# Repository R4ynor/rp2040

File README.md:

# rp2040
 rp2040 poor man's edition

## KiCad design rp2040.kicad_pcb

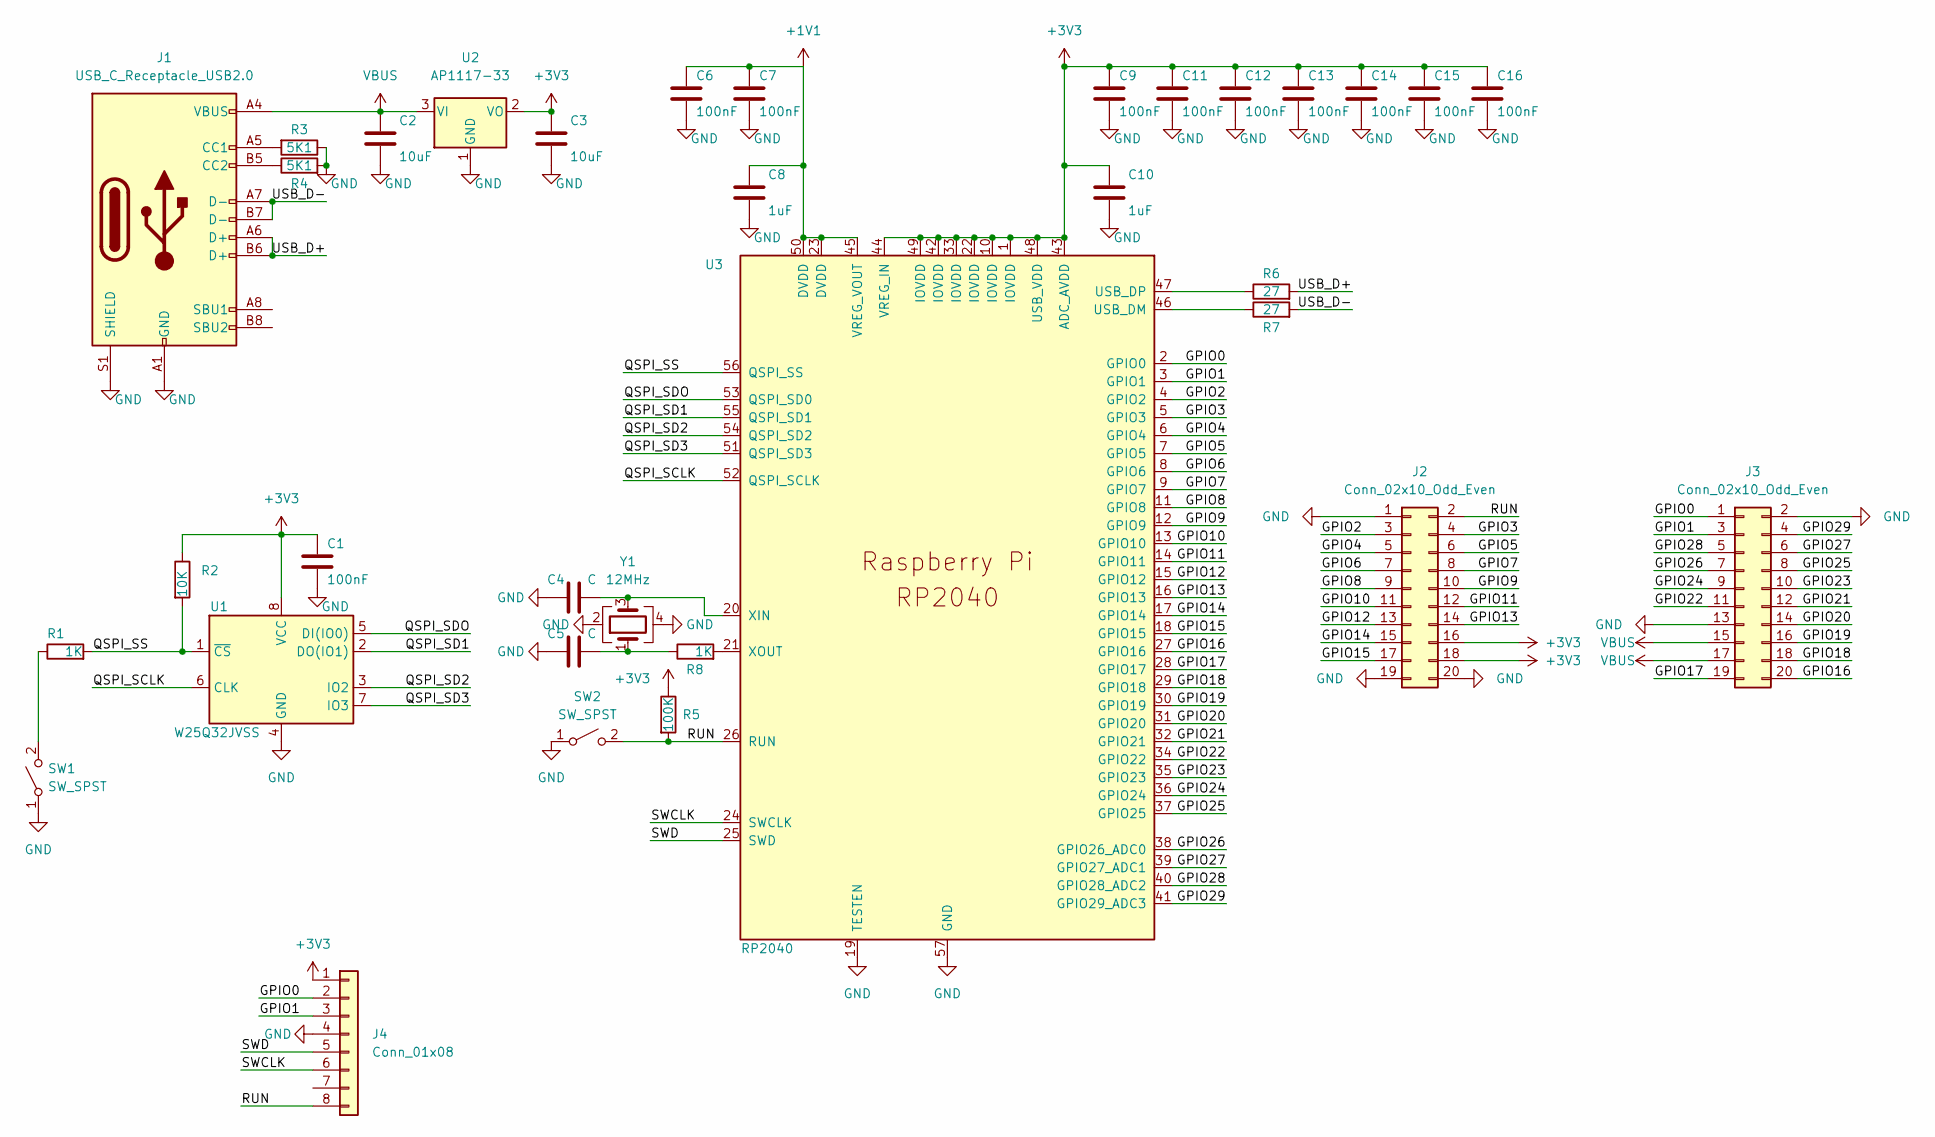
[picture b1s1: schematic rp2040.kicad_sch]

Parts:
C1, C6, C7, C9, C11, C12, C13, C14, C15, C16: 100nF; C_0402_1005Metric_Pad0.74x0.62mm_HandSolder
C2, C3: 10uF; C_0603_1608Metric_Pad1.08x0.95mm_HandSolder
C4, C5: C; C_0402_1005Metric_Pad0.74x0.62mm_HandSolder
C8, C10: 1uF; C_0402_1005Metric_Pad0.74x0.62mm_HandSolder
J1: USB_C_Receptacle_USB2.0; USB_C_Receptacle_XKB_U262-16XN-4BVC11
J2, J3: Conn_02x10_Odd_Even; PinHeader_2x10_P2.54mm_Vertical
J4: Conn_01x08; SOIC_clipProgSmall
R1, R8: 1K; R_0402_1005Metric_Pad0.72x0.64mm_HandSolder
R2: 10K; R_0402_1005Metric_Pad0.72x0.64mm_HandSolder
R3, R4: 5K1; R_0402_1005Metric_Pad0.72x0.64mm_HandSolder
R5: 100K; R_0402_1005Metric_Pad0.72x0.64mm_HandSolder
R6, R7: 27; R_0402_1005Metric_Pad0.72x0.64mm_HandSolder
SW1, SW2: SW_SPST; SW_3x4x2
U1: W25Q32JVSS; SOIC-USON-8
U2: AP1117-33; SOT-89-3
U3: RP2040; RP2040-QFN-56
Y1: 12MHz; Crystal_SMD_2520-4Pin_2.5x2.0mm

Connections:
+1V1: C6.1, C7.1, C8.1, U3.23 (DVDD), U3.45 (VREG_VOUT), U3.50 (DVDD)
+3V3: C1.1, C3.1, C9.1, C10.1, C11.1, C12.1, C13.1, C14.1, C15.1, C16.1, J2.16, J2.18, J4.1, R2.1, R5.1, U1.8 (VCC), U2.2 (VO), U3.1 (IOVDD), U3.10 (IOVDD), U3.22 (IOVDD), U3.33 (IOVDD), U3.42 (IOVDD), U3.43 (ADC_AVDD), U3.44 (VREG_IN), U3.48 (USB_VDD), U3.49 (IOVDD)
/GPIO0: J3.1, J4.2, U3.2 (GPIO0)
/GPIO1: J3.3, J4.3, U3.3 (GPIO1)
/GPIO2: J2.3, U3.4 (GPIO2)
/GPIO3: J2.4, U3.5 (GPIO3)
/GPIO4: J2.5, U3.6 (GPIO4)
/GPIO5: J2.6, U3.7 (GPIO5)
/GPIO6: J2.7, U3.8 (GPIO6)
/GPIO7: J2.8, U3.9 (GPIO7)
/GPIO8: J2.9, U3.11 (GPIO8)
/GPIO9: J2.10, U3.12 (GPIO9)
/GPIO10: J2.11, U3.13 (GPIO10)
/GPIO11: J2.12, U3.14 (GPIO11)
/GPIO12: J2.13, U3.15 (GPIO12)
/GPIO13: J2.14, U3.16 (GPIO13)
/GPIO14: J2.15, U3.17 (GPIO14)
/GPIO15: J2.17, U3.18 (GPIO15)
/GPIO16: J3.20, U3.27 (GPIO16)
/GPIO17: J3.19, U3.28 (GPIO17)
/GPIO18: J3.18, U3.29 (GPIO18)
/GPIO19: J3.16, U3.30 (GPIO19)
/GPIO20: J3.14, U3.31 (GPIO20)
/GPIO21: J3.12, U3.32 (GPIO21)
/GPIO22: J3.11, U3.34 (GPIO22)
/GPIO23: J3.10, U3.35 (GPIO23)
/GPIO24: J3.9, U3.36 (GPIO24)
/GPIO25: J3.8, U3.37 (GPIO25)
/GPIO26: J3.7, U3.38 (GPIO26_ADC0)
/GPIO27: J3.6, U3.39 (GPIO27_ADC1)
/GPIO28: J3.5, U3.40 (GPIO28_ADC2)
/GPIO29: J3.4, U3.41 (GPIO29_ADC3)
/QSPI_SCLK: U1.6 (CLK), U3.52 (QSPI_SCLK)
/QSPI_SD1: U1.2 (DO(IO1)), U3.55 (QSPI_SD1)
/QSPI_SD2: U1.3 (IO2), U3.54 (QSPI_SD2)
/QSPI_SD3: U1.7 (IO3), U3.51 (QSPI_SD3)
/QSPI_SDO: U1.5 (DI(IO0)), U3.53 (QSPI_SD0)
/QSPI_SS: R1.2, R2.2, U1.1 (~CS), U3.56 (QSPI_SS)
/RUN: J2.2, J4.8, R5.2, SW2.2 (B), U3.26 (RUN)
/SWCLK: J4.6, U3.24 (SWCLK)
/SWD: J4.5, U3.25 (SWD)
/USB_D+: J1.A6 (D+), J1.B6 (D+), R6.2
/USB_D-: J1.A7 (D-), J1.B7 (D-), R7.2
GND: C1.2, C2.2, C3.2, C4.1, C5.1, C6.2, C7.2, C8.2, C9.2, C10.2, C11.2, C12.2, C13.2, C14.2, C15.2, C16.2, J1.A1 (GND), J1.A12 (GND), J1.B1 (GND), J1.B12 (GND), J1.S1 (SHIELD), J2.1, J2.19, J2.20, J3.2, J3.13, J4.4, R3.1, R4.2, SW1.1 (A), SW2.1 (A), U1.4 (GND), U1.9 (GND), U2.1 (GND), U3.19 (TESTEN), U3.57 (GND), Y1.2, Y1.4
unnamed: C4.2, U3.20 (XIN), Y1.3
unnamed: C5.2, R8.1, Y1.1
unnamed: J1.A5 (CC1), R3.2
unnamed: J1.B5 (CC2), R4.1
unnamed: R1.1, SW1.2 (B)
unnamed: R6.1, U3.47 (USB_DP)
unnamed: R7.1, U3.46 (USB_DM)
unnamed: R8.2, U3.21 (XOUT)
VBUS: C2.1, J1.A4 (VBUS), J1.A9 (VBUS), J1.B4 (VBUS), J1.B9 (VBUS), J3.15, J3.17, U2.3 (VI)

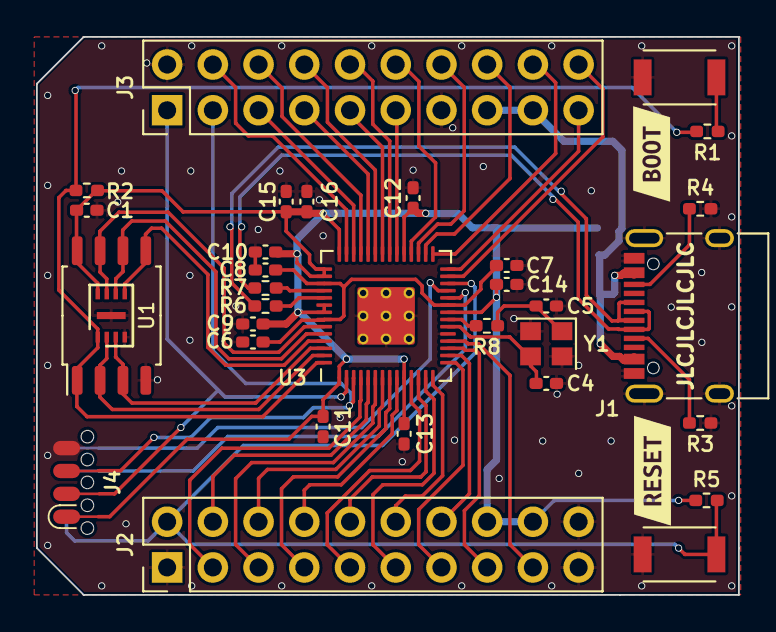
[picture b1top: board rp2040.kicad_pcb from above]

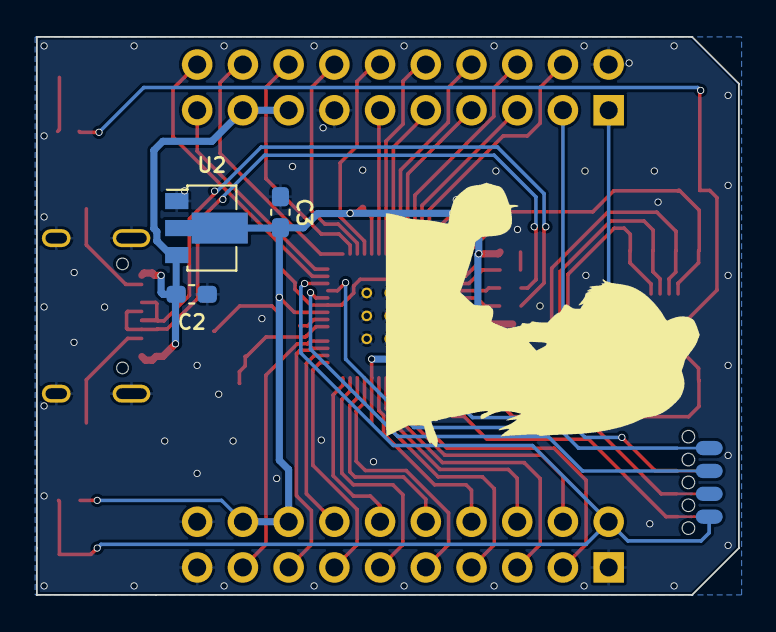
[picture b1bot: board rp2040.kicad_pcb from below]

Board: 2 copper layers, 39.0 x 31.0 mm, 36 parts (3 on the bottom side), 53 nets.

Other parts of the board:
kibuzzard-6203A46A: G***; kibuzzard-6203A46A
kibuzzard-6203A47E: G***; kibuzzard-6203A47E

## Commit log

2022-02-08 Footprint assignment
2022-02-09 Routing finished
2022-02-09 Some random tweaks
2022-02-10 Rearranged pinheaders, added logo and random tweaks
2022-02-16 Final touches for the manufacturing process
2022-05-26 Generate HTML BOM
